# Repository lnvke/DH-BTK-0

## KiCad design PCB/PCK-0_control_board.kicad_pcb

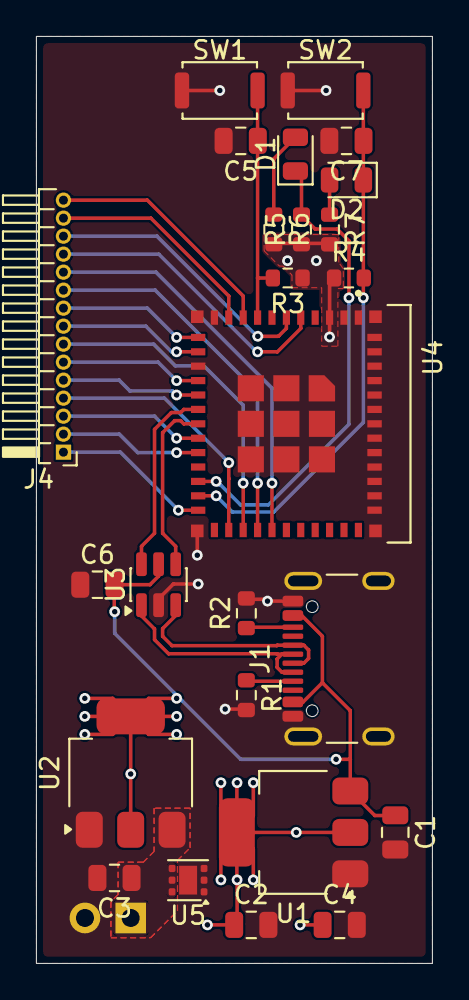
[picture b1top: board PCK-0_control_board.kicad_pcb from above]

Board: 4 copper layers, 22.0 x 51.5 mm, 26 parts (1 on the bottom side), 30 nets.

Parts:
BT1: Battery; PinHeader_1x02_P2.54mm_Horizontal
C1, C2, C3, C4: 10u; C_0805_2012Metric
C5, C6, C7: 100n; C_0805_2012Metric
D1: BOOT_IND; D_0805_2012Metric
D2: BOOT_LIGHT; D_0805_2012Metric
J1: USB_C_Receptacle_USB2.0_16P; USB_C_Receptacle_GCT_USB4105-xx-A_16P_TopMnt_Horizontal
J4: Conn_01x15; PinHeader_1x15_P1.00mm_Horizontal
R1, R2: 5k1; R_0603_1608Metric
R3, R4, R5: 10k; R_0603_1608Metric
R6, R7: 470; R_0603_1608Metric
SW1: EN; SW_Push_SPST_NO_Alps_SKRK
SW2: BOOT; SW_Push_SPST_NO_Alps_SKRK
U1, U2: NCP1117-3.3_SOT223; SOT-223-3_TabPin2
U3: USBLC6-2SC6; SOT-23-6
U4: ESP32-C6-MINI-1; XCVR_ESP32-C6-MINI-1U-H4
U5: TVS1400DRV; WSON-6-1EP_2x2mm_P0.65mm_EP1x1.6mm

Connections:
+3V3: C2.1, C4.1, R3.1, R4.1, R5.1, R6.2, R7.2, U1.2 (VO), U2.2 (VO), U4.3 (3V3)
/D+: J1.A6 (D+), J1.B6 (D+), U3.3 (I/O2)
/D-: J1.A7 (D-), J1.B7 (D-), U3.1 (I/O1)
/IO0: J4.9, U4.12 (IO0)
/IO1: J4.8, U4.13 (IO1)
/IO2: J4.12, U4.5 (IO2)
/IO3: J4.13, U4.6 (IO3)
/IO4: J4.15, U4.9 (IO4)
/IO5: J4.14, U4.10 (IO5)
/IO6: J4.6, U4.15 (IO6)
/IO7: J4.5, U4.16 (IO7)
/IO8: D1.1 (K), R5.2, U4.22 (IO8)
/IO9: C7.1, D2.1 (K), R4.2, SW2.2, U4.23 (IO9)
/IO14: J4.3, U4.19 (IO14)
/IO15: J4.2, U4.20 (IO15)
/IO18: J4.1, U4.24 (IO18)
/IO20: J4.4, U4.26 (IO20)
/IO21: J4.7, U4.27 (IO21)
/IO22: J4.10, U4.28 (IO22)
/IO23: J4.11, U4.29 (IO23)
/USB_D+: U3.4 (I/O2), U4.18 (IO13)
/USB_D-: U3.6 (I/O1), U4.17 (IO12)
GND: BT1.2 (-), C1.2, C2.2, C3.2, C4.2, C5.2, C6.1, C7.2, J1.A1 (GND), J1.A12 (GND), J1.B1 (GND), J1.B12 (GND), J1.SH (SHIELD), R1.2, R2.2, SW1.1, SW2.1, U1.1 (GND), U2.1 (GND), U3.2 (GND), U4.1 (GND), U4.2 (GND), U4.11 (GND), U4.14 (GND), U4.36 (GND), U4.37 (GND), U4.38 (GND), U4.39 (GND), U4.40 (GND), U4.41 (GND), U4.42 (GND), U4.43 (GND), U4.44 (GND), U4.45 (GND), U4.46 (GND), U4.47 (GND), U4.48 (GND), U4.49_1 (GND), U4.49_2 (GND), U4.49_3 (GND), U4.49_4 (GND), U4.49_5 (GND), U4.49_6 (GND), U4.49_7 (GND), U4.49_8 (GND), U4.49_9 (GND), U4.50 (GND), U4.51 (GND), U4.52 (GND), U4.53 (GND), U5.1 (GND), U5.2 (GND), U5.3 (GND), U5.7 (GND)
unnamed: D1.2 (A), R6.1
unnamed: D2.2 (A), R7.1
unnamed: J1.A5 (CC1), R1.1
unnamed: J1.B5 (CC2), R2.1
unnamed: C5.1, R3.2, SW1.2, U4.8 (EN)
VBAT: BT1.1 (+), C3.1, U2.3 (VI), U5.4 (IN), U5.5 (IN), U5.6 (IN)
VBUS: C1.1, C6.2, J1.A4 (VBUS), J1.A9 (VBUS), J1.B4 (VBUS), J1.B9 (VBUS), U1.3 (VI), U3.5 (VBUS)

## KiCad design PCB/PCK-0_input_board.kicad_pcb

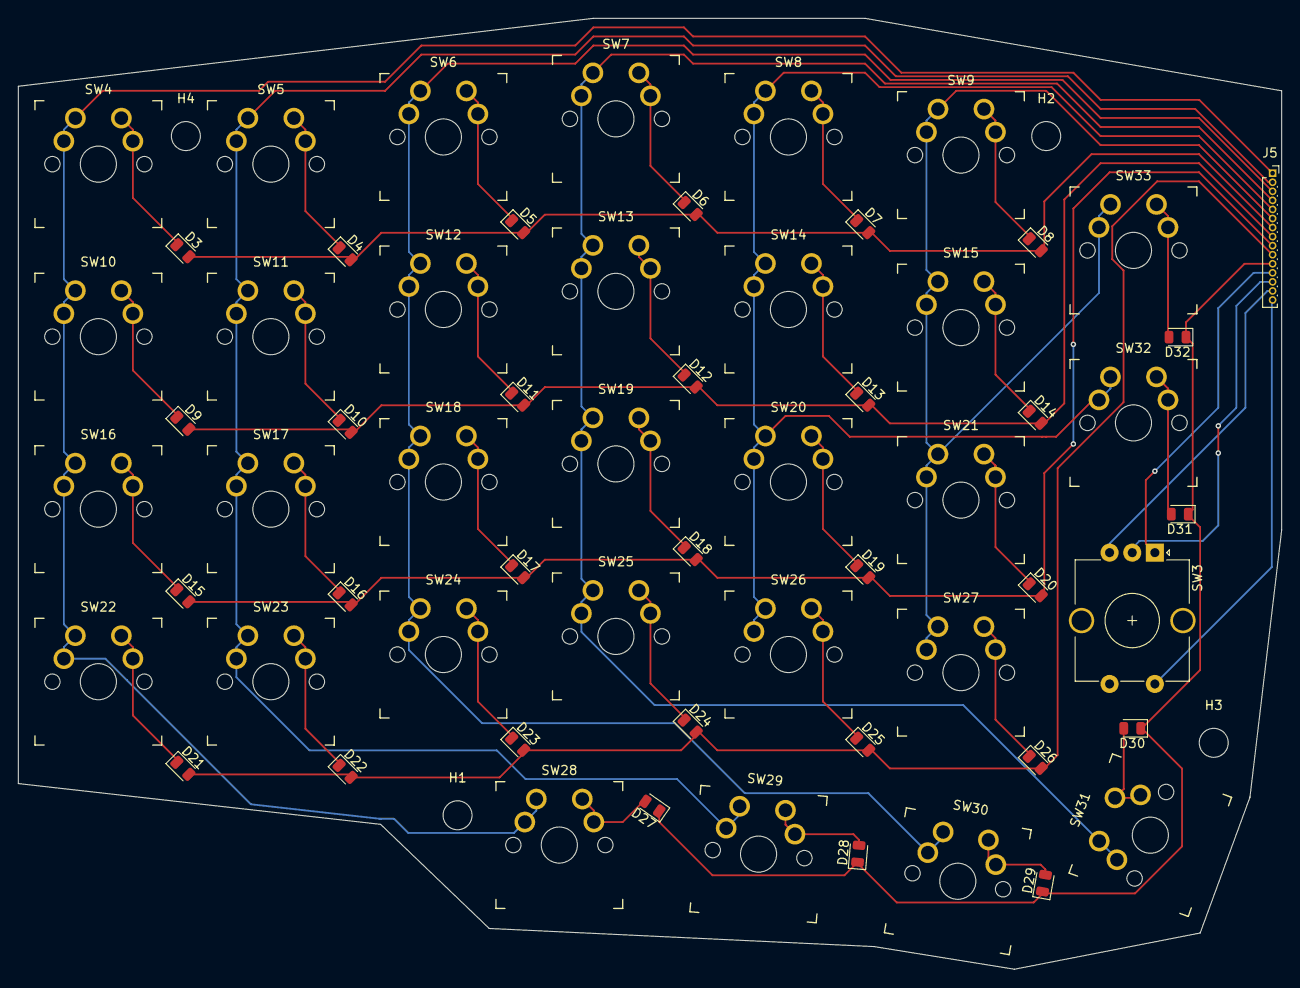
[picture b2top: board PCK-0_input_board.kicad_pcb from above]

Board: 4 copper layers, 139.5 x 105.0 mm, 66 parts (0 on the bottom side), 46 nets.

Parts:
D3, D4, D5, D6, D7, D8, D9, D10, D11, D12, D13, D14, D15, D16, D17, D18, D19, D20, D21, D22, D23, D24, D25, D26, D27, D28, D29, D30, D31, D32: D; D_0805_2012Metric
H1, H2, H3, H4: MountingHole_Pad; MountingHole_3.2mm_M3
J5: Conn_01x15_Socket; PinSocket_1x15_P1.00mm_Vertical
SW3: RotaryEncoder_Switch_MP; RotaryEncoder_Alps_EC12E-Switch_Vertical_H20mm_CircularMoun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
SW4: 1,1; SW_MX_reversible
SW5: 2,1; SW_MX_reversible
SW6: 3,1; SW_MX_reversible
SW7: 4,1; SW_MX_reversible
SW8: 5,1; SW_MX_reversible
SW9: 6,1; SW_MX_reversible
SW10: 1,2; SW_MX_reversible
SW11: 2,2; SW_MX_reversible
SW12: 3,2; SW_MX_reversible
SW13: 4,2; SW_MX_reversible
SW14: 5,2; SW_MX_reversible
SW15: 6,2; SW_MX_reversible
SW16: 1,3; SW_MX_reversible
SW17: 2,3; SW_MX_reversible
SW18: 3,3; SW_MX_reversible
SW19: 4,3; SW_MX_reversible
SW20: 5,3; SW_MX_reversible
SW21: 6,3; SW_MX_reversible
SW22, SW28: 1,4; SW_MX_reversible
SW23, SW29: 2,4; SW_MX_reversible
SW24, SW30: 3,4; SW_MX_reversible
SW25, SW31: 4,4; SW_MX_reversible
SW26, SW32: 5,4; SW_MX_reversible
SW27, SW33: 6,4; SW_MX_reversible

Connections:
/IO0: D3.1 (K), D4.1 (K), D5.1 (K), D6.1 (K), D7.1 (K), D8.1 (K), J5.7
/IO1: D9.1 (K), D10.1 (K), D11.1 (K), D12.1 (K), D13.1 (K), D14.1 (K), J5.8
/IO2: J5.4, SW7.1, SW13.1, SW19.1, SW25.1, SW31.1
/IO3: J5.3, SW6.1, SW12.1, SW18.1, SW24.1, SW30.1
/IO4: J5.1, SW4.1, SW10.1, SW16.1, SW22.1, SW28.1
/IO5: J5.2, SW5.1, SW11.1, SW17.1, SW23.1, SW29.1
/IO6: D21.1 (K), D22.1 (K), D23.1 (K), D24.1 (K), D25.1 (K), D26.1 (K), J5.10
/IO7: D27.1 (K), D28.1 (K), D29.1 (K), D30.1 (K), D31.1 (K), D32.1 (K), J5.11
/IO14: J5.13, SW3.C
/IO15: J5.14, SW3.B
/IO18: J5.15, SW3.S1
/IO20: J5.12, SW3.A
/IO21: D15.1 (K), D16.1 (K), D17.1 (K), D18.1 (K), D19.1 (K), D20.1 (K), J5.9
/IO22: J5.6, SW9.1, SW15.1, SW21.1, SW27.1, SW33.1
/IO23: J5.5, SW8.1, SW14.1, SW20.1, SW26.1, SW32.1
GND: SW3.MP, SW3.S2
unnamed: D3.2 (A), SW4.2
unnamed: D4.2 (A), SW5.2
unnamed: D5.2 (A), SW6.2
unnamed: D6.2 (A), SW7.2
unnamed: D7.2 (A), SW8.2
unnamed: D8.2 (A), SW9.2
unnamed: D9.2 (A), SW10.2
unnamed: D10.2 (A), SW11.2
unnamed: D11.2 (A), SW12.2
unnamed: D12.2 (A), SW13.2
unnamed: D13.2 (A), SW14.2
unnamed: D14.2 (A), SW15.2
unnamed: D15.2 (A), SW16.2
unnamed: D16.2 (A), SW17.2
unnamed: D17.2 (A), SW18.2
unnamed: D18.2 (A), SW19.2
unnamed: D19.2 (A), SW20.2
unnamed: D20.2 (A), SW21.2
unnamed: D21.2 (A), SW22.2
unnamed: D22.2 (A), SW23.2
unnamed: D23.2 (A), SW24.2
unnamed: D24.2 (A), SW25.2
unnamed: D25.2 (A), SW26.2
unnamed: D26.2 (A), SW27.2
unnamed: D27.2 (A), SW28.2
unnamed: D28.2 (A), SW29.2
unnamed: D29.2 (A), SW30.2
unnamed: D30.2 (A), SW31.2
unnamed: D31.2 (A), SW32.2
unnamed: D32.2 (A), SW33.2

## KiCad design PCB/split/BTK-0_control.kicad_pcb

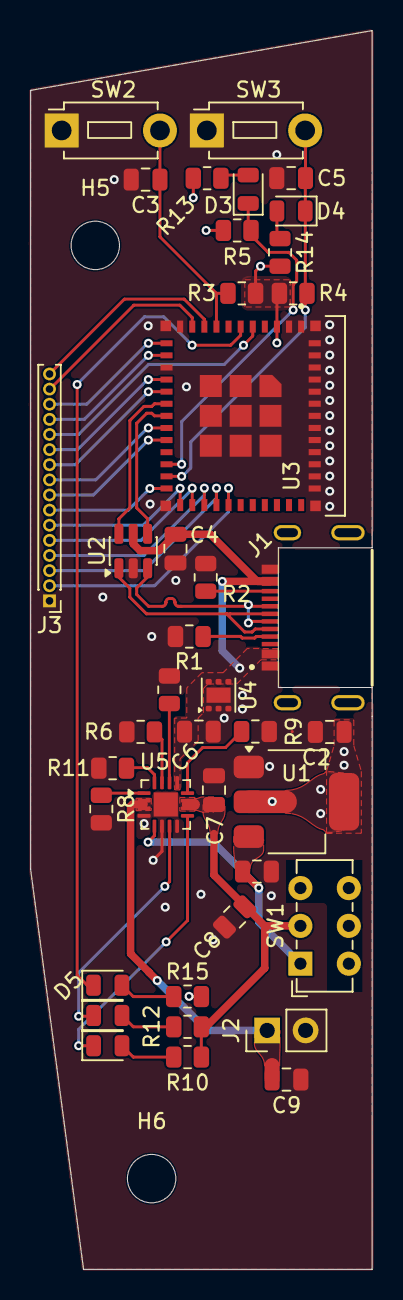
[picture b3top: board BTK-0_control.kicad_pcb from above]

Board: 4 copper layers, 22.6 x 81.9 mm, 42 parts (0 on the bottom side), 43 nets.

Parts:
C1, C2: 10u; C_0805_2012Metric
C3, C4, C5: 100n; C_0805_2012Metric
C6, C7, C8, C9: 4.7u; C_0805_2012Metric
D1, D2: LED; LED_0805_2012Metric
D3: MODE_IND; LED_0805_2012Metric
D4: BOOT_IND; LED_0805_2012Metric
D5: TXRX_IND; LED_0805_2012Metric
H5, H6: MountingHole_Pad; MountingHole_3.2mm_M3_ISO7380
J1: USB_C_Receptacle_USB2.0_16P; GCT_USB4510-03-1-A_REVA
J2: Battery; PinHeader_1x02_P2.54mm_Vertical
J3: Conn_01x16_Pin; PinHeader_1x16_P1.00mm_Vertical
R1, R2: 5k1; R_0805_2012Metric
R3, R4, R5, R6, R8: 10k; R_0805_2012Metric
R7: 27k; R_0805_2012Metric
R9: 1.5k; R_0805_2012Metric
R10, R12: 1k; R_0805_2012Metric
R11: 4.7k; R_0805_2012Metric
R13, R14, R15: 470; R_0805_2012Metric
SW1: SW_SPDT; SW_E-Switch_EG1271_SPDT
SW2: EN; SW_PUSH_1P1T_6x3.5mm_H4.3_APEM_MJTP1243
SW3: BOOT; SW_PUSH_1P1T_6x3.5mm_H4.3_APEM_MJTP1243
U1: NCP1117-3.3_SOT223; SOT-223-3_TabPin2
U2: USBLC6-2SC6; SOT-23-6
U3: ESP32-C6-MINI-1; XCVR_ESP32-C6-MINI-1U-H4
U4: TVS1400DRV; WSON-6-1EP_2x2mm_P0.65mm_EP1x1.6mm
U5: BQ24075RGT; VQFN-16-1EP_3x3mm_P0.5mm_EP1.6x1.6mm

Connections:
+3V3: C2.1, R3.1, R4.1, R5.1, R13.2, R14.2, R15.2, U1.2 (VO), U3.3 (3V3)
/D+: J1.A6 (D+), J1.B6 (D+), U2.3 (I/O2)
/D-: J1.A7 (D-), J1.B7 (D-), U2.1 (I/O1)
/IO0: J3.14, U3.12 (IO0)
/IO1: J3.13, U3.13 (IO1)
/IO2: J3.12, U3.5 (IO2)
/IO3: D5.1 (K), U3.6 (IO3)
/IO4: J3.16, U3.9 (IO4)
/IO5: J3.15, U3.10 (IO5)
/IO6: J3.11, U3.15 (IO6)
/IO7: J3.10, U3.16 (IO7)
/IO8: D3.1 (K), R5.2, U3.22 (IO8)
/IO9: C5.1, D4.1 (K), R4.2, SW3.2, U3.23 (IO9)
/IO14: J3.9, U3.19 (IO14)
/IO15: J3.8, U3.20 (IO15)
/IO18: J3.7, U3.24 (IO18)
/IO19: J3.6, U3.25 (IO19)
/IO20: J3.5, U3.26 (IO20)
/IO21: J3.4, U3.27 (IO21)
/IO22: J3.3, U3.28 (IO22)
/IO23: J3.2, U3.29 (IO23)
/USB_D+: U2.4 (I/O2), U3.18 (IO13)
/USB_D-: U2.6 (I/O1), U3.17 (IO12)
GND: C1.2, C2.2, C3.2, C4.1, C5.2, C6.2, C7.2, C8.2, C9.2, J1.A1 (GND), J1.A12 (GND), J1.B1 (GND), J1.B12 (GND), J2.2, J3.1, R1.2, R2.2, R6.1, R7.1, R8.2, R9.1, R11.2, SW2.1, SW3.1, U1.1 (GND), U2.2 (GND), U3.1 (GND), U3.2 (GND), U3.11 (GND), U3.14 (GND), U3.36 (GND), U3.37 (GND), U3.38 (GND), U3.39 (GND), U3.40 (GND), U3.41 (GND), U3.42 (GND), U3.43 (GND), U3.44 (GND), U3.45 (GND), U3.46 (GND), U3.47 (GND), U3.48 (GND), U3.49_1 (GND), U3.49_2 (GND), U3.49_3 (GND), U3.49_4 (GND), U3.49_5 (GND), U3.49_6 (GND), U3.49_7 (GND), U3.49_8 (GND), U3.49_9 (GND), U3.50 (GND), U3.51 (GND), U3.52 (GND), U3.53 (GND), U4.1 (GND), U4.2 (GND), U4.3 (GND), U4.7 (GND), U5.4 (~CE), U5.6 (EN1), U5.8 (VSS), U5.17 (VSS)
unnamed: D1.2 (A), R10.2
unnamed: D1.1 (K), U5.7 (~PGOOD)
unnamed: D2.2 (A), R12.1
unnamed: D2.1 (K), U5.9 (~CHG)
unnamed: D3.2 (A), R13.1
unnamed: D4.2 (A), R14.1
unnamed: D5.2 (A), R15.1
unnamed: J1.A5 (CC1), R1.1
unnamed: J1.B5 (CC2), R2.1
unnamed: C3.1, R3.2, SW2.2, U3.8 (EN)
unnamed: R9.2, U5.12 (ILIM)
unnamed: R11.1, U5.16 (ISET)
unnamed: R6.2, U5.15 (SYSOFF)
unnamed: R7.2, U5.14 (TMR)
unnamed: R8.1, U5.1 (TS)
VBAT: C9.1, J2.1, U5.2 (BAT), U5.3 (BAT)
VBUS: C4.2, C6.1, J1.A4 (VBUS), J1.A9 (VBUS), J1.B4 (VBUS), J1.B9 (VBUS), U2.5 (VBUS), U4.4 (IN), U4.5 (IN), U4.6 (IN), U5.13 (IN)
VCC: C1.1, SW1.1 (A), U1.3 (VI), U5.5 (EN2)
VOUT: C7.1, C8.1, R10.1, R12.2, SW1.2 (B), U5.10 (OUT), U5.11 (OUT)

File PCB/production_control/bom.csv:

Designator,Footprint,Quantity,Value,LCSC Part #
"C1, C2, C7",0805,3,10u,
"C3, C4, C5",0805,3,100n,
"C6, C8, C9",0805,3,4.7u,
"D1, D2",0805,2,LED,
D3,0805,1,MODE_IND,
D4,0805,1,BOOT_IND,
D5,0805,1,TXRX_IND,
J1,GCT_USB4510-03-1-A_REVA,1,USB_C_Receptacle_USB2.0_16P,
J2,PinHeader_1x02_P2.54mm_Vertical,1,Battery,
J3,PinHeader_1x16_P1.00mm_Vertical,1,Conn_01x16_Pin,
"R1, R2",0805,2,5k1,
"R10, R12",0805,2,1k,
R11,0805,1,4.7k,
"R13, R14, R15",0805,3,470,
"R3, R4, R5, R6, R8",0805,5,10k,
R7,0805,1,27k,
R9,0805,1,1.5k,
"SW1, SW2",SW_JS102011SAQN,2,SW_SPDT,
SW3,SW_PUSH_1P1T_6x3.5mm_H4.3_APEM_MJTP1243,1,EN,
SW4,SW_PUSH_1P1T_6x3.5mm_H4.3_APEM_MJTP1243,1,BOOT,
U1,SOT-223-3_TabPin2,1,NCP1117-3.3_SOT223,
U2,SOT-23-6,1,USBLC6-2SC6,
U3,XCVR_ESP32-C6-MINI-1U-H4,1,ESP32-C6-MINI-1,
U4,WSON-6-1EP_2x2mm_P0.65mm_EP1x1.6mm,1,TVS1400DRV,
U5,VQFN-16-1EP_3x3mm_P0.5mm_EP1.6x1.6mm,1,BQ24075RGT,

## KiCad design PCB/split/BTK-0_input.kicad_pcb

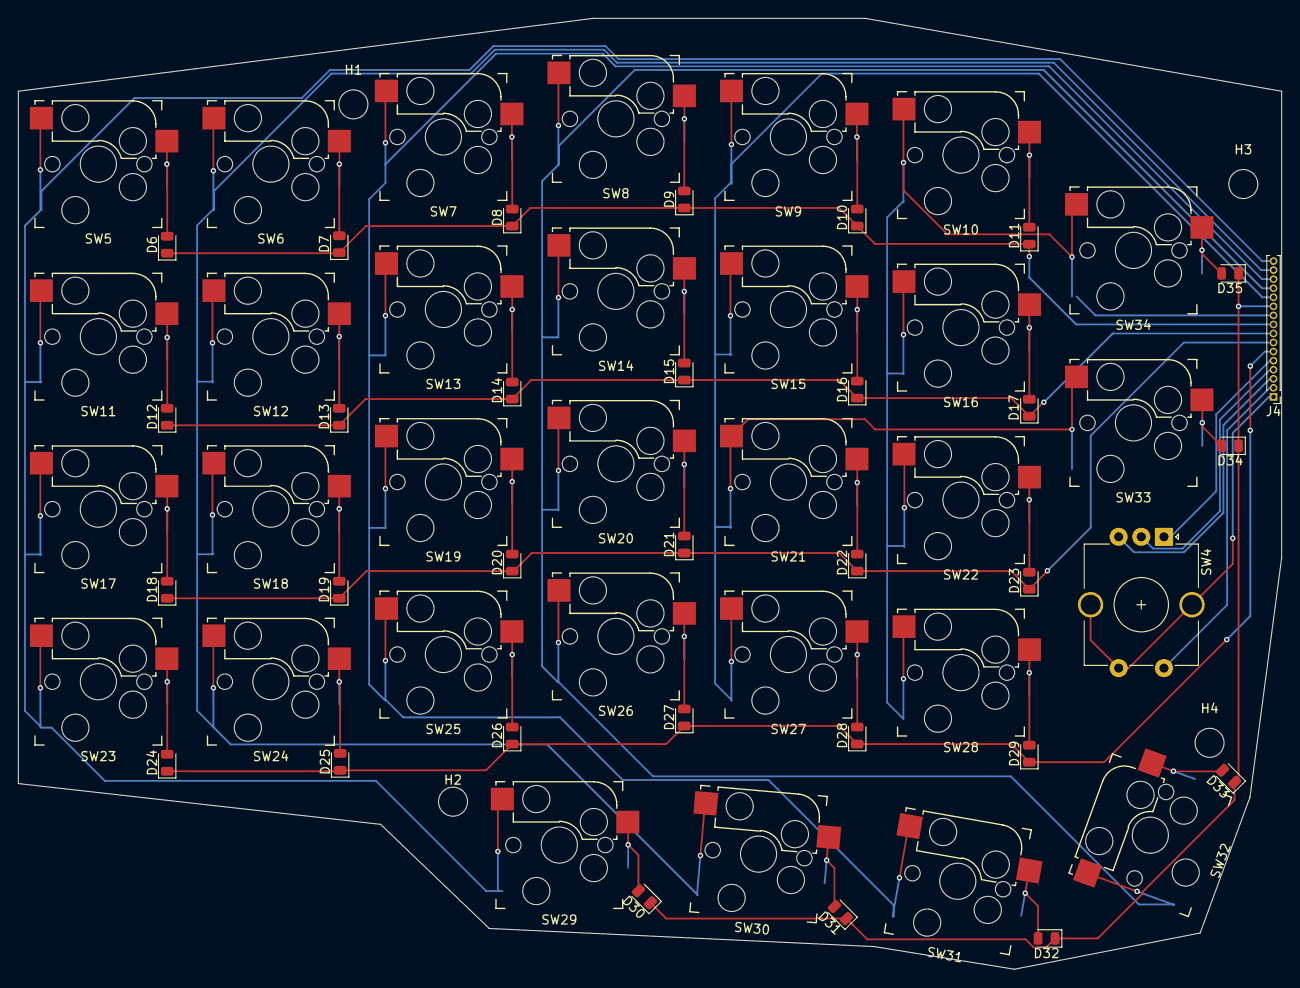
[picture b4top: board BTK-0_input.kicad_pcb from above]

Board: 4 copper layers, 139.5 x 105.0 mm, 66 parts (0 on the bottom side), 46 nets.

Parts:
D6, D7, D8, D9, D10, D11, D12, D13, D14, D15, D16, D17, D18, D19, D20, D21, D22, D23, D24, D25, D26, D27, D28, D29, D30, D31, D32, D33, D34, D35: D; D_0805_2012Metric
H1, H2, H3, H4: MountingHole_Pad; MountingHole_3.2mm_M3_ISO7380
J4: Conn_01x16_Socket; PinHeader_1x16_P1.00mm_Vertical
SW4: RotaryEncoder_Switch_MP; RotaryEncoder_Alps_EC12E-Switch_Vertical_H20mm_CircularMoun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
SW5: 1,1; Kailh_socket_MX_reversible
SW6: 2,1; Kailh_socket_MX_reversible
SW7: 3,1; Kailh_socket_MX_reversible
SW8: 4,1; Kailh_socket_MX_reversible
SW9: 5,1; Kailh_socket_MX_reversible
SW10: 6,1; Kailh_socket_MX_reversible
SW11: 1,2; Kailh_socket_MX_reversible
SW12: 2,2; Kailh_socket_MX_reversible
SW13: 3,2; Kailh_socket_MX_reversible
SW14: 4,2; Kailh_socket_MX_reversible
SW15: 5,2; Kailh_socket_MX_reversible
SW16: 6,2; Kailh_socket_MX_reversible
SW17: 1,3; Kailh_socket_MX_reversible
SW18: 2,3; Kailh_socket_MX_reversible
SW19: 3,3; Kailh_socket_MX_reversible
SW20: 4,3; Kailh_socket_MX_reversible
SW21: 5,3; Kailh_socket_MX_reversible
SW22: 6,3; Kailh_socket_MX_reversible
SW23, SW29: 1,4; Kailh_socket_MX_reversible
SW24, SW30: 2,4; Kailh_socket_MX_reversible
SW25, SW31: 3,4; Kailh_socket_MX_reversible
SW26, SW32: 4,4; Kailh_socket_MX_reversible
SW27, SW33: 5,4; Kailh_socket_MX_reversible
SW28, SW34: 6,4; Kailh_socket_MX_reversible

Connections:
/IO0: J4.14, SW7.1, SW13.1, SW19.1, SW25.1, SW31.1
/IO1: J4.13, SW8.1, SW14.1, SW20.1, SW26.1, SW32.1
/IO2: J4.12, SW9.1, SW15.1, SW21.1, SW27.1, SW33.1
/IO4: J4.16, SW5.1, SW11.1, SW17.1, SW23.1, SW29.1
/IO5: J4.15, SW6.1, SW12.1, SW18.1, SW24.1, SW30.1
/IO6: D30.1 (K), D31.1 (K), D32.1 (K), D33.1 (K), D34.1 (K), D35.1 (K), J4.11
/IO7: J4.10, SW10.1, SW16.1, SW22.1, SW28.1, SW34.1
/IO14: D6.1 (K), D7.1 (K), D8.1 (K), D9.1 (K), D10.1 (K), D11.1 (K), J4.9
/IO15: D12.1 (K), D13.1 (K), D14.1 (K), D15.1 (K), D16.1 (K), D17.1 (K), J4.8
/IO18: D18.1 (K), D19.1 (K), D20.1 (K), D21.1 (K), D22.1 (K), D23.1 (K), J4.7
/IO19: D24.1 (K), D25.1 (K), D26.1 (K), D27.1 (K), D28.1 (K), D29.1 (K), J4.6
/IO20: J4.5, SW4.A
/IO21: J4.4, SW4.C
/IO22: J4.3, SW4.B
/IO23: J4.2, SW4.S1
GND: J4.1, SW4.MP, SW4.S2
unnamed: D6.2 (A), SW5.2
unnamed: D7.2 (A), SW6.2
unnamed: D8.2 (A), SW7.2
unnamed: D9.2 (A), SW8.2
unnamed: D10.2 (A), SW9.2
unnamed: D11.2 (A), SW10.2
unnamed: D12.2 (A), SW11.2
unnamed: D13.2 (A), SW12.2
unnamed: D14.2 (A), SW13.2
unnamed: D15.2 (A), SW14.2
unnamed: D16.2 (A), SW15.2
unnamed: D17.2 (A), SW16.2
unnamed: D18.2 (A), SW17.2
unnamed: D19.2 (A), SW18.2
unnamed: D20.2 (A), SW19.2
unnamed: D21.2 (A), SW20.2
unnamed: D22.2 (A), SW21.2
unnamed: D23.2 (A), SW22.2
unnamed: D24.2 (A), SW23.2
unnamed: D25.2 (A), SW24.2
unnamed: D26.2 (A), SW25.2
unnamed: D27.2 (A), SW26.2
unnamed: D28.2 (A), SW27.2
unnamed: D29.2 (A), SW28.2
unnamed: D30.2 (A), SW29.2
unnamed: D31.2 (A), SW30.2
unnamed: D32.2 (A), SW31.2
unnamed: D33.2 (A), SW32.2
unnamed: D34.2 (A), SW33.2
unnamed: D35.2 (A), SW34.2
